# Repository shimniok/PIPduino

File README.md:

PIPduino
========

A 'duino clone you can Put In a Project. Small, breadboard-friendly 'duinos are compact and work
great on a breadboard. But you need a baseboard to embed them in a project.

PIPduino already has ports for I2C, SPI, Serial/FTDI, and servo-style connectors with VCC and GND
for each analog and digital pin.  It has a beefy regulator on board, too.

Buy one now on [Tindie](https://www.tindie.com/products/bot_thoughts/pipduino/).

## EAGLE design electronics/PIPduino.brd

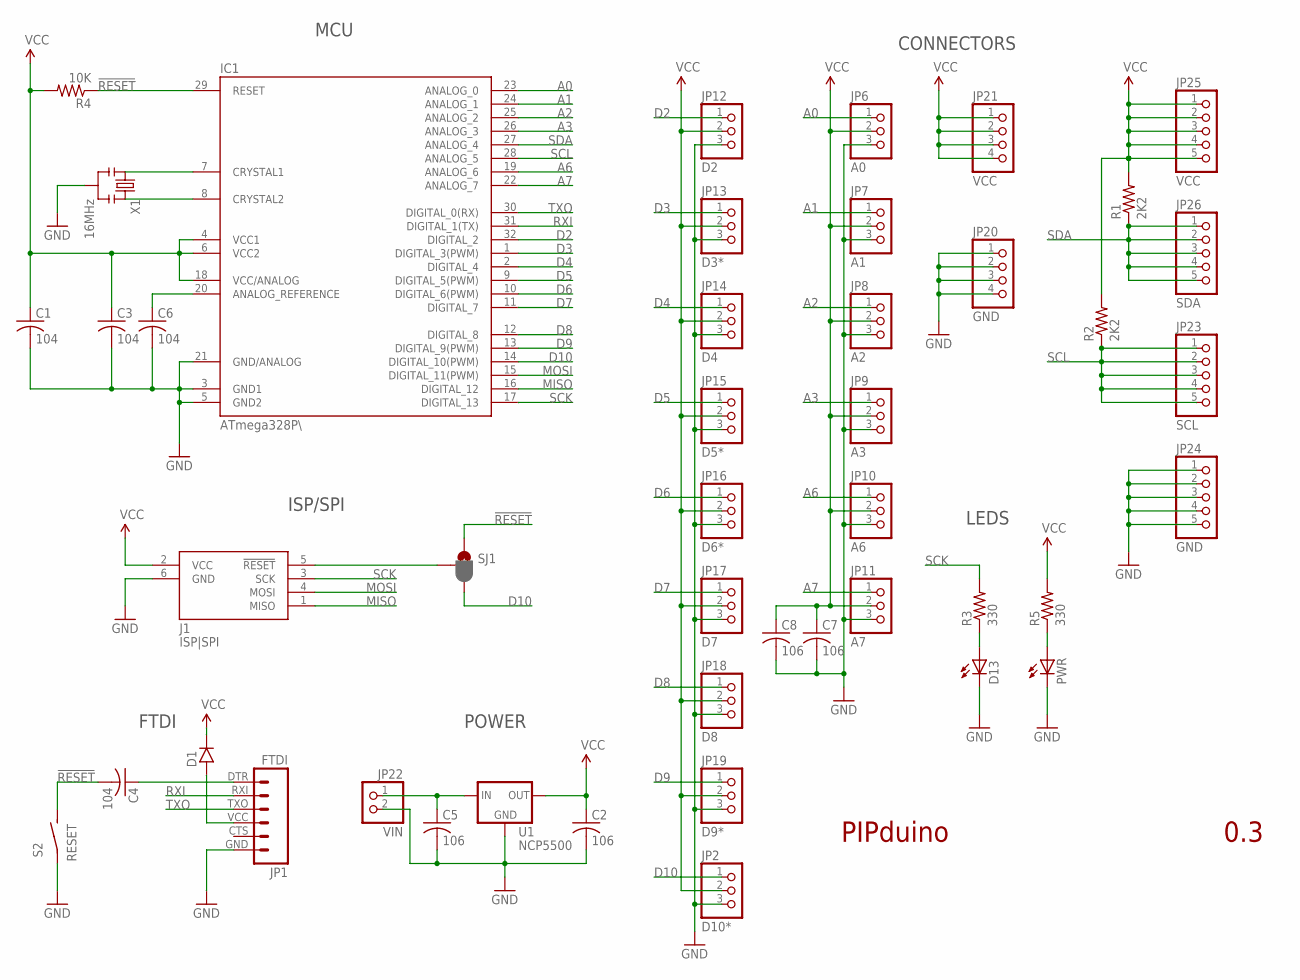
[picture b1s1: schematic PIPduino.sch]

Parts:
C1, C3, C4, C6: 104; C0603
C2, C5, C7, C8: 106; C1206
D1: DIODE_SOD123FL; SOD123FL
D13: LED3MM
IC1: ATmega328P\; TQFP32-08
J1: ISP|SPI; CON6P2R
JP1: FTDI; FTDI_BASIC
JP2: D10*; 1X03-S
JP6: A0; 1X03-S
JP7: A1; 1X03-S
JP8: A2; 1X03-S
JP9: A3; 1X03-S
JP10: A6; 1X03-S
JP11: A7; 1X03-S
JP12: D2; 1X03-S
JP13: D3*; 1X03-S
JP14: D4; 1X03-S
JP15: D5*; 1X03-S
JP16: D6*; 1X03-S
JP17: D7; 1X03-S
JP18: D8; 1X03-S
JP19: D9*; 1X03-S
JP20: GND; 1X04-S
JP21: VCC; 1X04-S
JP22: VIN; 1X02-S
JP23: SCL; 1X05-S
JP24: GND; 1X05-S
JP25: VCC; 1X05-S
JP26: SDA; 1X05-S
PWR: LED3MM
R1, R2: 2K2; R0603
R3, R5: 330; R0603
R4: 10K; R0603
S2: RESET; 3X4X2TACT
SJ1: JUMPER-PAD-3-2OF3_NC_BY_PASTE; PAD-JUMPER-3-2OF3_NC_BY_PASTE_YES_SILK_FULL_BOX
U1: NCP5500; DPAK
X1: 16MHz; CSTCE_V_C

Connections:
!RESET: C4.2, IC1.29 (RESET), R4.1, S2.P$2 (S), SJ1.1
A0: IC1.23 (ANALOG_0), JP6.1
A1: IC1.24 (ANALOG_1), JP7.1
A2: IC1.25 (ANALOG_2), JP8.1
A3: IC1.26 (ANALOG_3), JP9.1
A6: IC1.19 (ANALOG_6), JP10.1
A7: IC1.22 (ANALOG_7), JP11.1
D2: IC1.32 (DIGITAL_2), JP12.1
D3: IC1.1 (DIGITAL_3(PWM)), JP13.1
D4: IC1.2 (DIGITAL_4), JP14.1
D5: IC1.9 (DIGITAL_5(PWM)), JP15.1
D6: IC1.10 (DIGITAL_6(PWM)), JP16.1
D7: IC1.11 (DIGITAL_7), JP17.1
D8: IC1.12 (DIGITAL_8), JP18.1
D9: IC1.13 (DIGITAL_9(PWM)), JP19.1
D10: IC1.14 (DIGITAL_10(PWM)), JP2.1, SJ1.3
GND: C1.2, C2.2, C3.2, C5.2, C6.2, C7.2, C8.2, D13.K (C), IC1.3 (GND1), IC1.5 (GND2), IC1.21 (GND/ANALOG), J1.6 (GND), JP1.GND (6), JP2.3, JP6.3, JP7.3, JP8.3, JP9.3, JP10.3, JP11.3, JP12.3, JP13.3, JP14.3, JP15.3, JP16.3, JP17.3, JP18.3, JP19.3, JP20.1, JP20.2, JP20.3, JP20.4, JP22.2, JP24.1, JP24.2, JP24.3, JP24.4, JP24.5, PWR.K (C), S2.P$1, U1.4 (GND), X1.GND
MISO: IC1.16 (DIGITAL_12), J1.1 (MISO)
MOSI: IC1.15 (DIGITAL_11(PWM)), J1.4 (MOSI)
unnamed: D13.A, R3.1
unnamed: C5.1, JP22.1, U1.1 (VIN)
unnamed: J1.5 (!RESET), SJ1.2
unnamed: PWR.A, R5.1
unnamed: D1.A, JP1.VCC (4)
unnamed: C6.1, IC1.20 (ANALOG_REFERENCE)
unnamed: IC1.7 (CRYSTAL1), X1.X1
unnamed: IC1.8 (CRYSTAL2), X1.X2
unnamed: C4.1, JP1.DTR (1)
RXI: IC1.31 (DIGITAL_1(TX)), JP1.RXI (2)
SCK: IC1.17 (DIGITAL_13), J1.3 (SCK), R3.2
SCL: IC1.28 (ANALOG_5), JP23.1, JP23.2, JP23.3, JP23.4, JP23.5, R2.1
SDA: IC1.27 (ANALOG_4), JP26.1, JP26.2, JP26.3, JP26.4, JP26.5, R1.1
TXO: IC1.30 (DIGITAL_0(RX)), JP1.TXO (3)
VCC: C1.1, C2.1, C3.1, C7.1, C8.1, D1.C, IC1.4 (VCC1), IC1.6 (VCC2), IC1.18 (VCC/ANALOG), J1.2 (VCC), JP2.2, JP6.2, JP7.2, JP8.2, JP9.2, JP10.2, JP11.2, JP12.2, JP13.2, JP14.2, JP15.2, JP16.2, JP17.2, JP18.2, JP19.2, JP21.1, JP21.2, JP21.3, JP21.4, JP25.1, JP25.2, JP25.3, JP25.4, JP25.5, R1.2, R2.2, R4.2, R5.2, U1.3 (VOUT)

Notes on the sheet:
FTDI
POWER
ISP/SPI
MCU
CONNECTORS
LEDS
PIPduino
0.3

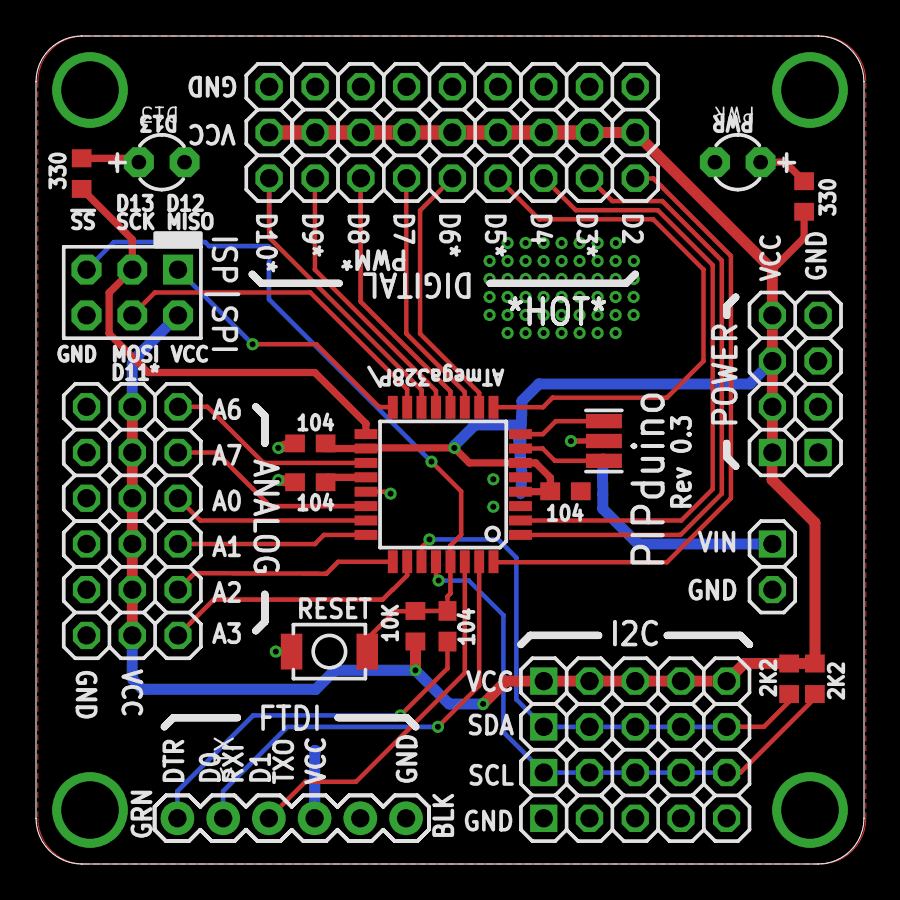
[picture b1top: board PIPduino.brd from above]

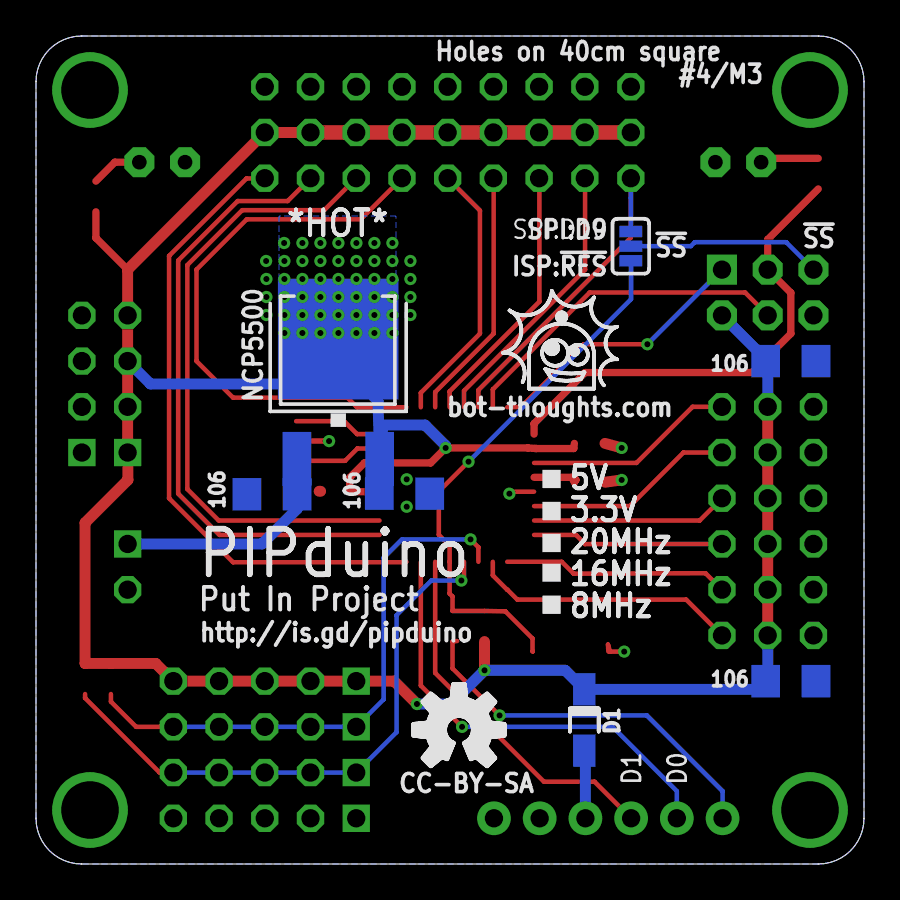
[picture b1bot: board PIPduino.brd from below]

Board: 2 copper layers, 46.0 x 46.0 mm, 45 parts (7 on the bottom side), 34 nets.

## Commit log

2014-08-15 R0.1 as ordered
2014-08-15 Added 5th I2C, fixed silk for VIN
2014-08-26 Revised power pin silk to be more visible; moved rev silk to make room.
2014-08-26 Fixed silk text "spin" setting
2014-08-26 Surrounded top screw holes with GND
2014-08-26 Removed top 5V polygon, star pattern power, 106's on analog, 104 on aref, larger power traces, removed polygons on top mounting holes
2014-08-26 added bootloader. Minor board tweaks
2014-08-28 Added link to Tindie product in README.md
2014-09-02 Final LDO regulator selection, rearrangement, silk updates, fixed missing D10
2014-09-02 Fixed missing checkboxes in silk
2014-09-02 Fixed some silk errors
2015-12-01 migrated wiki to documentation readme
2015-12-01 updated sale link
2015-12-01 converted pinout section to tables, improved descriptions
2015-12-01 Various updates to README
2015-12-01 Improved thermal design, minor silk fixes, revised LED design for 330 ohm reflow DFM
2015-12-02 moved eagle/gerber files into electronics subdir
2015-12-02 Fixed !SS silk error
2015-12-02 minor silk corrections, moved D13/PWR labels, corrected 40cm->40mm, updated 3mm LED pkg + sign
2015-12-02 Updated 3-way jumper selector
2015-12-02 updated FTDI pin silk labels
2017-06-07 updated makefile to use pre-built hex, changed targets for installing bootloader
2017-06-07 removed unused hex/lst files
2017-06-07 removed unused hex/lst, .h, and make files
2017-06-07 added github readme
2017-06-07 added message while sleeping between commands (for Dragon)

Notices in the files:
electronics/PIPduino.brd:
CC-BY-SA
parts and their libraries:
SparkFun-Passives: Licensing: CC v3.0 Share-Alike You are welcome to use this library for commercial purposes.
